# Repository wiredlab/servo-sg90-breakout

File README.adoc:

= (Re)Build a servo from parts
from an SG-90 servo

*Migrated to GitLab: https://gitlab.com/wiredlab/sg90-servo-breakout[^]*

== TODO

* [x] Check pot polarity against labels and rotation.
* [x] Check motor polarity against labels and rotation.

== SG-90 modification

Remove the PCB from an SG-90.
Breakout the motor wires and pot wires.

JST PH 1.0mm 5-pin connector `BM05B-SRSS-TB` or `SM05B-SRSS-TB` for right-angle or normal to the board cable exit direction.

image::board-front.png[]

image::board-back.png[]

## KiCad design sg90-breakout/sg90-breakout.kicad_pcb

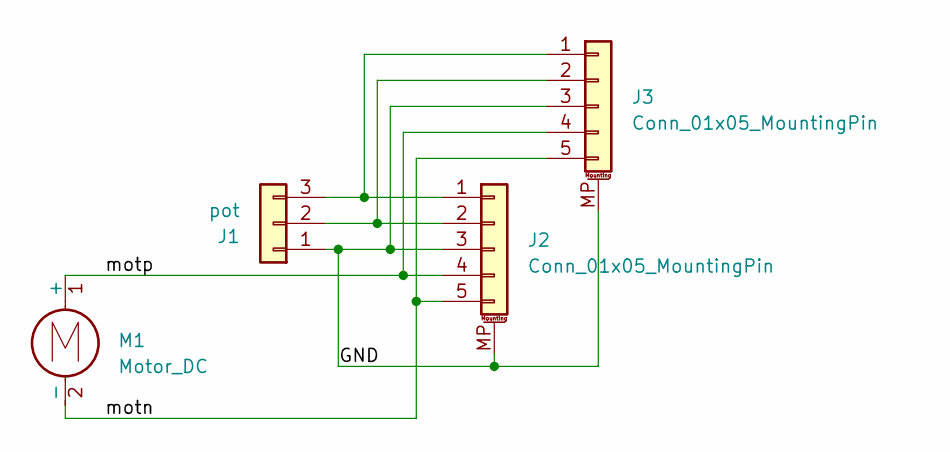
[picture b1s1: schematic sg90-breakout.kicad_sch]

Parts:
J1: pot; PinHeader_1x03_P2.54mm_Vertical
J2: Conn_01x05_MountingPin; JST_SH_BM05B-SRSS-TB_1x05-1MP_P1.00mm_Vertical
J3: Conn_01x05_MountingPin; JST_SH_SM05B-SRSS-TB_1x05-1MP_P1.00mm_Horizontal
M1: Motor_DC; sg90_motor

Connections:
/GND: J1.1, J2.3, J2.MP (MountPin), J3.3, J3.MP (MountPin)
/motn: J2.5, J3.5, M1.2 (-)
/motp: J2.4, J3.4, M1.1 (+)
unnamed: J1.2, J2.2, J3.2
unnamed: J1.3, J2.1, J3.1

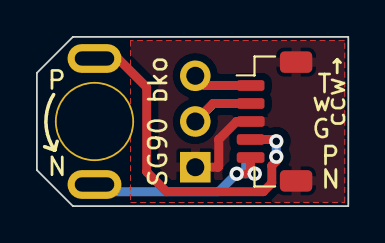
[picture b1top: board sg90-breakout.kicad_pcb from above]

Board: 2 copper layers, 17.3 x 9.4 mm, 4 parts (1 on the bottom side), 5 nets.

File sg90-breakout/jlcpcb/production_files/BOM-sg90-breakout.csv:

Comment,Designator,Footprint,LCSC
Conn_01x05_MountingPin,J2,JST_SH_BM05B-SRSS-TB_1x05-1MP_P1.00mm_Vertical,C160391
Conn_01x05_MountingPin,J3,JST_SH_SM05B-SRSS-TB_1x05-1MP_P1.00mm_Horizontal,C189896
Motor_DC,M1,sg90_motor,
pot,J1,PinHeader_1x03_P2.54mm_Vertical,

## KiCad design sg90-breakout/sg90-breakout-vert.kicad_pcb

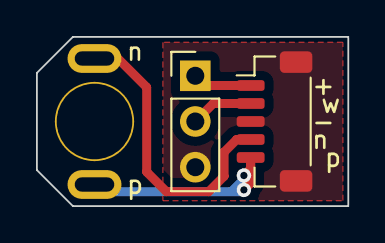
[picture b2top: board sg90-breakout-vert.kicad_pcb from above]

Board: 2 copper layers, 17.3 x 9.4 mm, 3 parts (0 on the bottom side), 5 nets.

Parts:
J1: Conn_01x03; PinHeader_1x03_P2.54mm_Vertical
J2: Conn_01x05_MountingPin; JST_SH_BM05B-SRSS-TB_1x05-1MP_P1.00mm_Vertical
M1: Motor_DC; sg90_motor

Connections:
/motn: J2.4, M1.2 (-)
/motp: J2.5, M1.1 (+)
GND: J1.3, J2.3, J2.MP (MountPin)
unnamed: J1.1, J2.1
unnamed: J1.2, J2.2

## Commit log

2024-02-26 Include production files
2024-02-26 Add board pic
2024-03-04 add TODO
2024-03-04 vertical and horizontal connector footprints
2024-03-05 tweak silkscreen
2024-03-05 Renumber pins to match rotations
    Viewed from top:
    * counter-clockwise is increasing pulse-width for normal servo
    * positive P-N to motor gives CCW output rotation
    * CCW rotation moves pot wiper towards "top" of pot
2024-03-05 Add JLC tag for production
2024-03-07 remove JLC order number tag
2024-03-07 Board renders for v1 tag
2024-04-19 Add servo modification pics
2024-07-06 Migrate to GitLab
